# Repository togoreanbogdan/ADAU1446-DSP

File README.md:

# ADAU1446-DSP
Project for ADAU1446 Audio DSP. The PCB is compatible with all the family ADAU144x.

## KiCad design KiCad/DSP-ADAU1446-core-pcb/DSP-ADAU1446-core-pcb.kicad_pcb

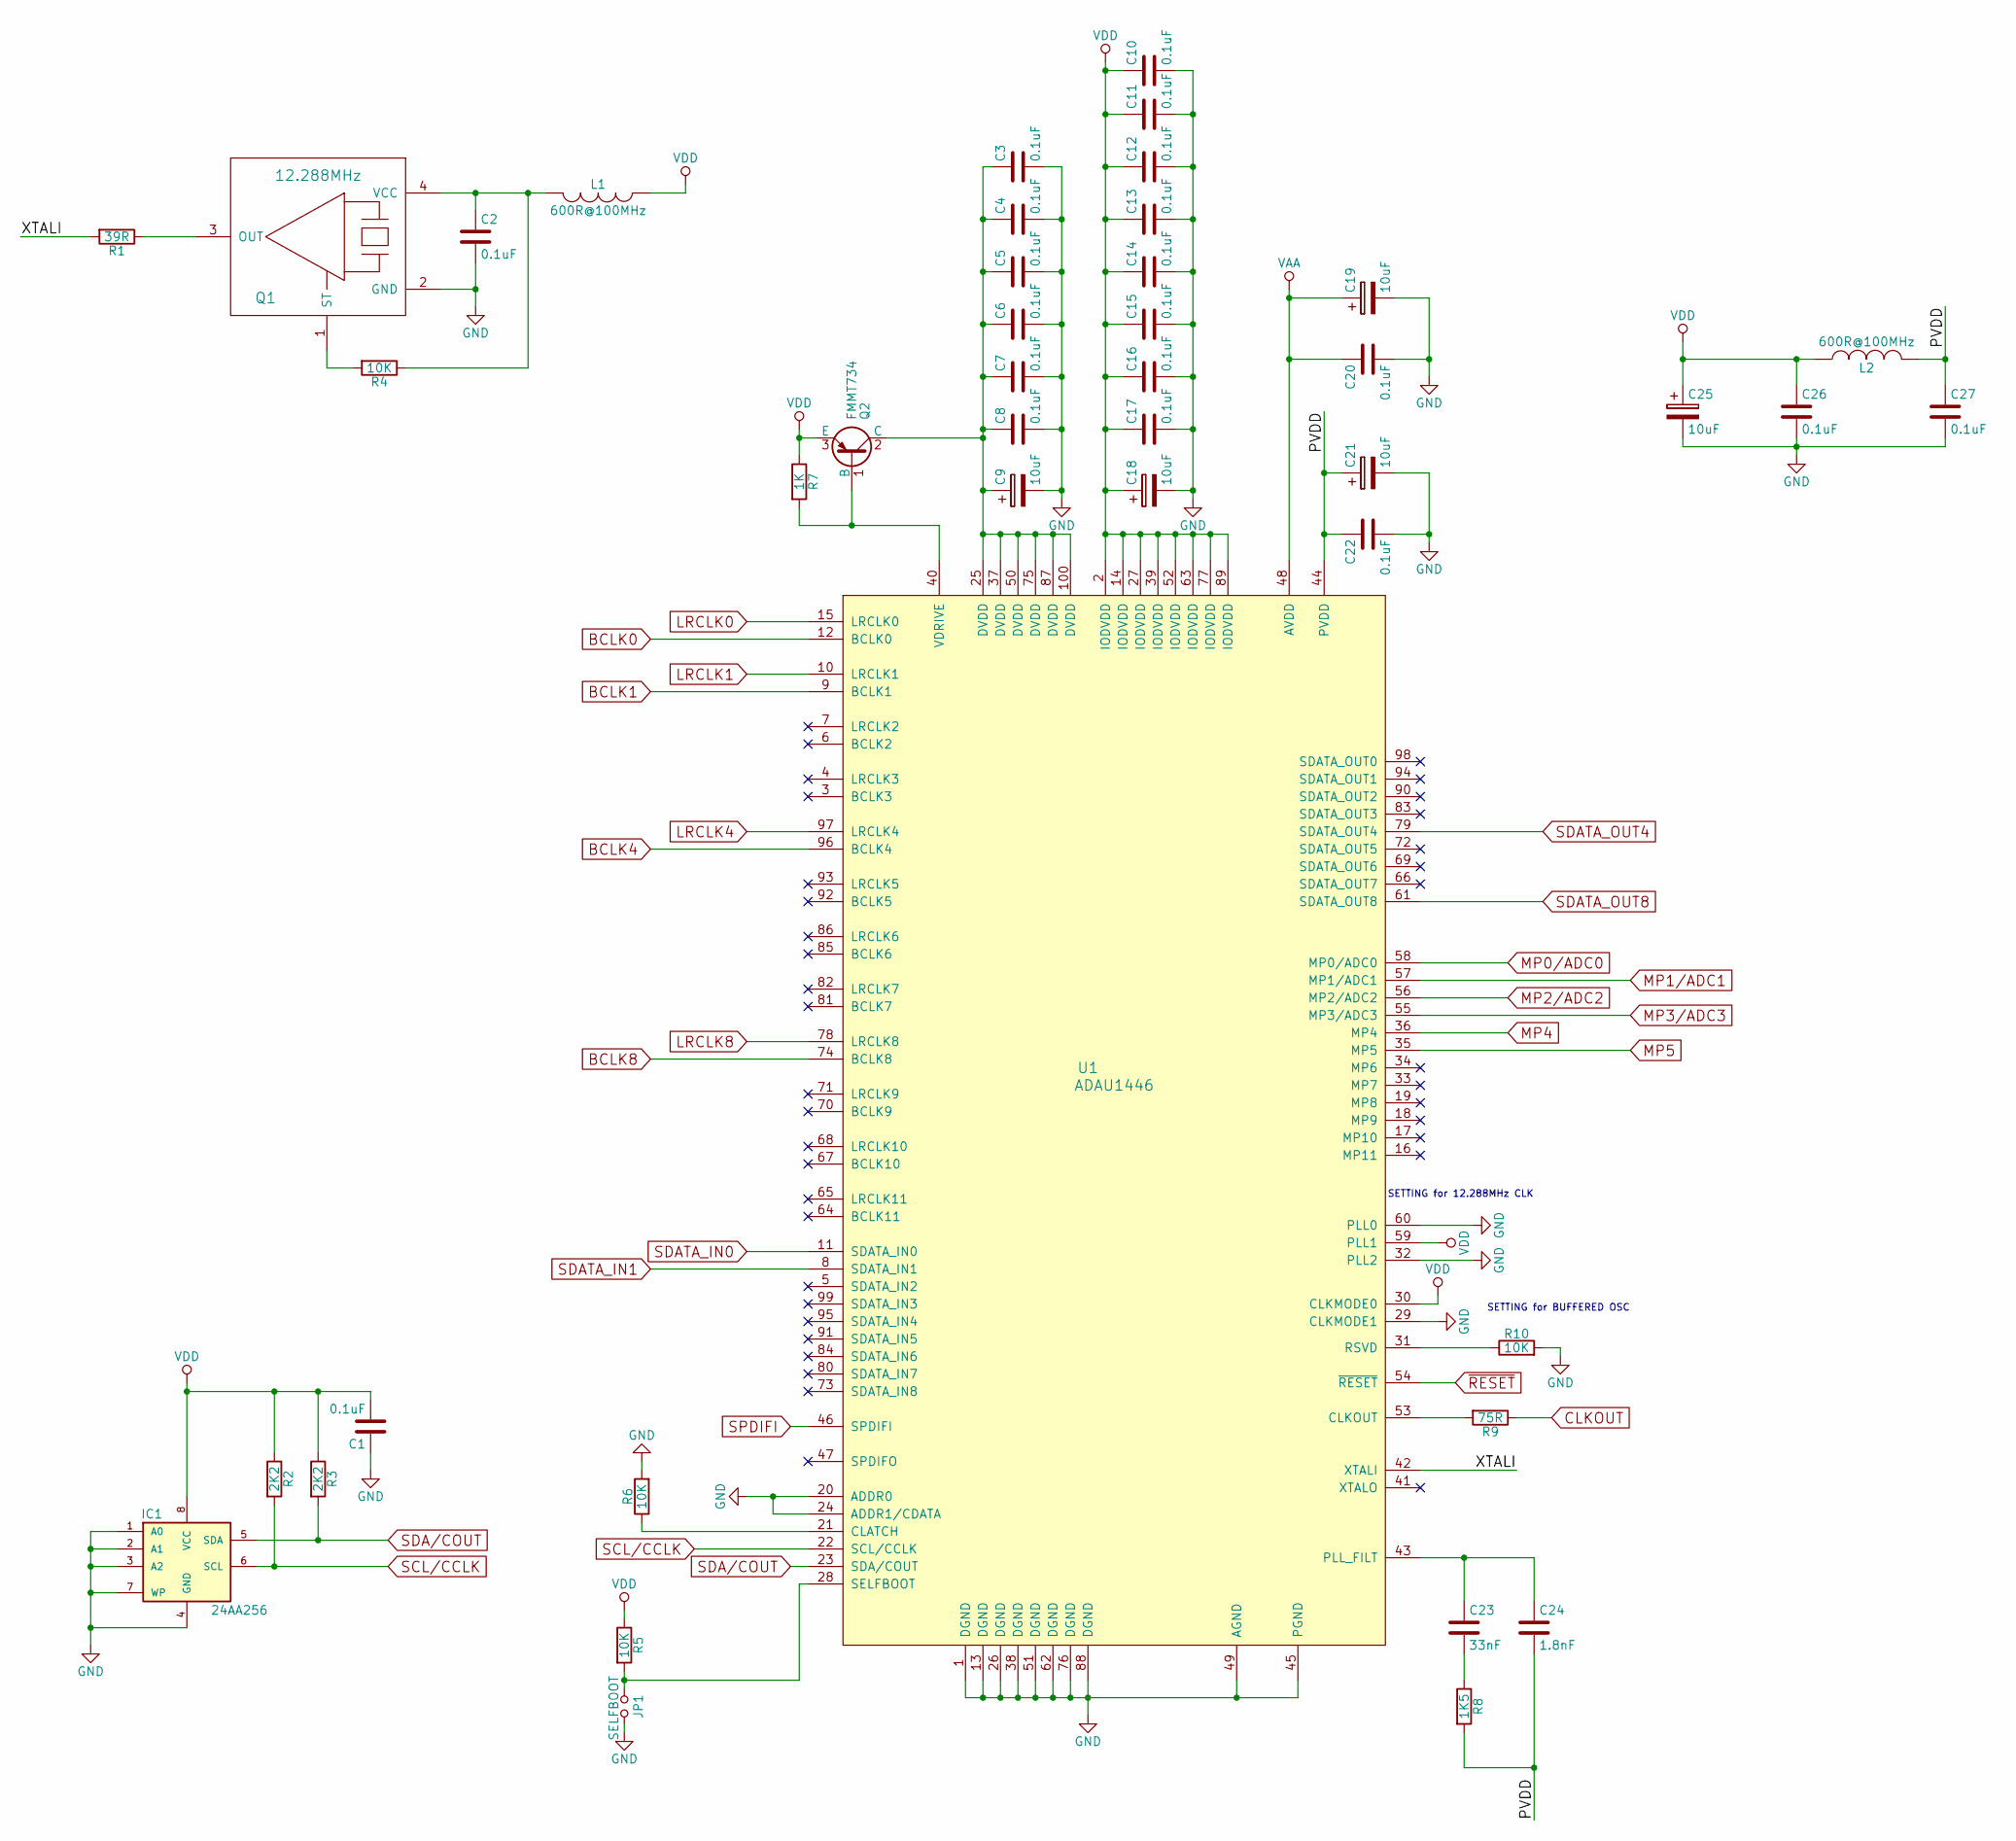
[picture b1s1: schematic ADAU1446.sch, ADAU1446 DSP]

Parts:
C1, C2, C3, C4, C5, C6, C7, C8, C10, C11, C12, C13, C14, C15, C16, C17, C20, C22, C26, C27: 0.1uF; c_0603
C9, C18: 10uF; c_elec_4x5.3; Mfr. Part No. EEE-FC1C100R
C19, C21, C25: 10uF; c_elec_4x5.3
C23: 33nF; c_0603
C24: 1.8nF; c_0603
IC1: 24AA256; so-8
JP1: SELFBOOT; pin_socket_2
L1, L2: 600R@100MHz; inductor_smd_0603
Q1: 12.288MHz; crystal_epson; Mfr. Part No. SG-210STF 12.2880ML3
Q2: FMMT734; sot23
R1: 39R; r_0603
R2, R3: 2K2; r_0603
R4, R5, R6, R10: 10K; r_0603
R7: 1K; r_0603
R8: 1K5; r_0603
R9: 75R; r_0603
U1: ADAU1446; TQFP-100

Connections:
/ADAU1446/PVDD: C21.1, C22.1, C24.2, C27.1, L2.2, R8.2, U1.44 (PVDD)
/ADAU1446/XTALI: R1.2, U1.42 (XTALI)
BCLK0: U1.12 (BCLK0); also elsewhere on the board
BCLK1: U1.9 (BCLK1); also elsewhere on the board
BCLK4: U1.96 (BCLK4); also elsewhere on the board
BCLK8: U1.74 (BCLK8); also elsewhere on the board
CLKOUT: R9.1; also elsewhere on the board
GND: C1.1, C2.2, C3.2, C4.2, C5.2, C6.2, C7.2, C8.2, C9.2, C10.2, C11.2, C12.2, C13.2, C14.2, C15.2, C16.2, C17.2, C18.2, C19.2, C20.2, C21.2, C22.2, C25.2, C26.2, C27.2, IC1.1 (A0), IC1.2 (A1), IC1.3 (A2), IC1.4 (GND), IC1.7 (WP), JP1.2, Q1.2 (GND), R6.2, R10.2, U1.1 (DGND), U1.13 (DGND), U1.20 (ADDR0), U1.24 (ADDR1/CDATA), U1.26 (DGND), U1.29 (CLKMODE1), U1.32 (PLL2), U1.38 (DGND), U1.45 (PGND), U1.49 (AGND), U1.51 (DGND), U1.60 (PLL0), U1.62 (DGND), U1.76 (DGND), U1.88 (DGND); also elsewhere on the board
LRCLK0: U1.15 (LRCLK0); also elsewhere on the board
LRCLK1: U1.10 (LRCLK1); also elsewhere on the board
LRCLK4: U1.97 (LRCLK4); also elsewhere on the board
LRCLK8: U1.78 (LRCLK8); also elsewhere on the board
MP0/ADC0: U1.58 (MP0/ADC0); also elsewhere on the board
MP1/ADC1: U1.57 (MP1/ADC1); also elsewhere on the board
MP2/ADC2: U1.56 (MP2/ADC2); also elsewhere on the board
MP3/ADC3: U1.55 (MP3/ADC3); also elsewhere on the board
MP4: U1.36 (MP4); also elsewhere on the board
MP5: U1.35 (MP5); also elsewhere on the board
unnamed: C2.1, L1.2, Q1.4 (VCC), R4.1
unnamed: C3.1, C4.1, C5.1, C6.1, C7.1, C8.1, C9.1, Q2.2 (C), U1.25 (DVDD), U1.37 (DVDD), U1.50 (DVDD), U1.75 (DVDD), U1.87 (DVDD), U1.100 (DVDD)
unnamed: C23.1, C24.1, U1.43 (PLL_FILT)
unnamed: C23.2, R8.1
unnamed: JP1.1, R5.2, U1.28 (SELFBOOT)
unnamed: Q1.1 (ST), R4.2
unnamed: Q1.3 (OUT), R1.1
unnamed: Q2.1 (B), R7.2, U1.40 (VDRIVE)
unnamed: R6.1, U1.21 (CLATCH)
unnamed: R9.2, U1.53 (CLKOUT)
unnamed: R10.1, U1.31 (RSVD)
SCL/CCLK: IC1.6 (SCL), R2.2, U1.22 (SCL/CCLK); also elsewhere on the board
SDA/COUT: IC1.5 (SDA), R3.2, U1.23 (SDA/COUT); also elsewhere on the board
SDATA_IN0: U1.11 (SDATA_IN0); also elsewhere on the board
SDATA_IN1: U1.8 (SDATA_IN1); also elsewhere on the board
SDATA_OUT4: U1.79 (SDATA_OUT4); also elsewhere on the board
SDATA_OUT8: U1.61 (SDATA_OUT8); also elsewhere on the board
SPDIFI: U1.46 (SPDIFI); also elsewhere on the board
VAA: C19.1, C20.1, U1.48 (AVDD); also elsewhere on the board
VDD: C1.2, C10.1, C11.1, C12.1, C13.1, C14.1, C15.1, C16.1, C17.1, C18.1, C25.1, C26.1, IC1.8 (VCC), L1.1, L2.1, Q2.3 (E), R2.1, R3.1, R5.1, R7.1, U1.2 (IODVDD), U1.14 (IODVDD), U1.27 (IODVDD), U1.30 (CLKMODE0), U1.39 (IODVDD), U1.52 (IODVDD), U1.59 (PLL1), U1.63 (IODVDD), U1.77 (IODVDD), U1.89 (IODVDD); also elsewhere on the board
~RESET: U1.54 (~RESET); also elsewhere on the board

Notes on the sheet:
SETTING for 12.288MHz CLK
SETTING for BUFFERED OSC

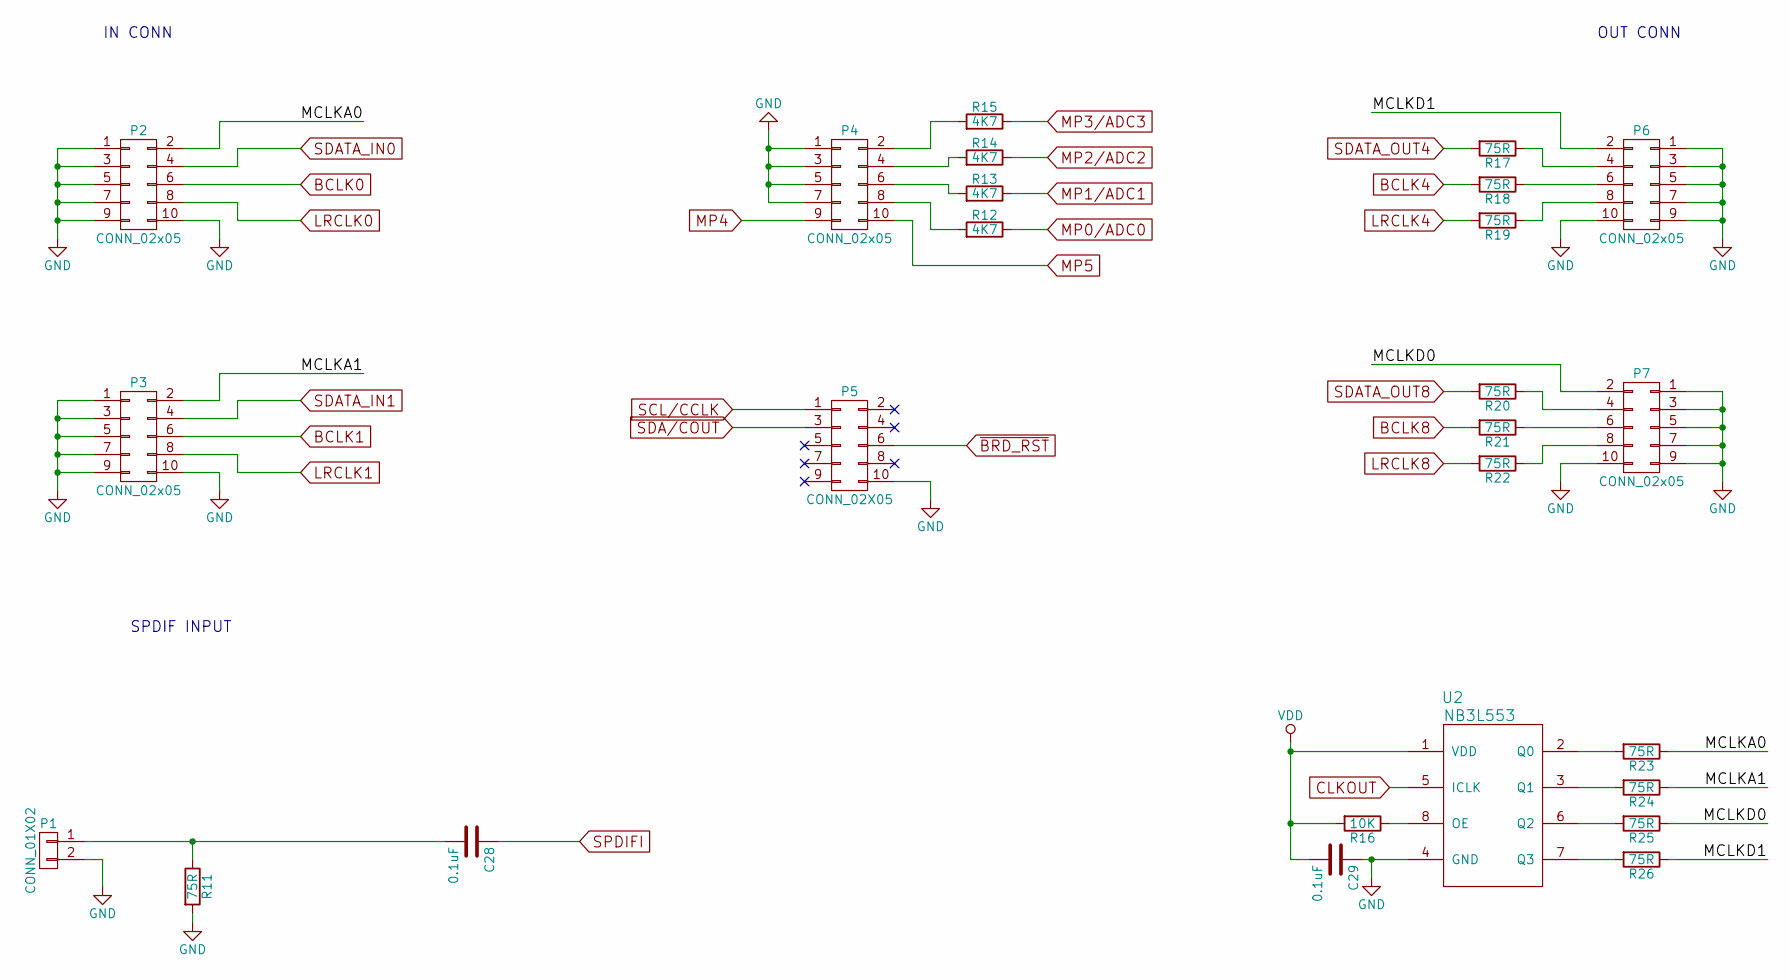
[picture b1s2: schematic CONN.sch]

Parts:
C28, C29: 0.1uF; c_0603
P1: CONN_01X02; Socket_Strip_Straight_1x02_Pitch2.54mm
P2, P3, P4, P6, P7: CONN_02x05; pin_strip_2mm_5x2; Mfr. Part No. DS1018-02-10B2
P5: CONN_02X05; pin_strip_2mm_5x2; Mfr. Part No. DS1018-02-10B2
R11, R17, R18, R19, R20, R21, R22, R23, R24, R25, R26: 75R; r_0603
R12, R13, R14, R15: 4K7; r_0603
R16: 10K; r_0603
U2: NB3L553; so-8; Mfr. Part No. NB3L553DG

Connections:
/CONN/MCLKA0: P2.2, R23.1
/CONN/MCLKA1: P3.2, R24.1
/CONN/MCLKD0: P7.2, R25.1
/CONN/MCLKD1: P6.2, R26.1
BCLK0: P2.6; also elsewhere on the board
BCLK1: P3.6; also elsewhere on the board
BCLK4: R18.2; also elsewhere on the board
BCLK8: R21.2; also elsewhere on the board
CLKOUT: U2.5 (ICLK); also elsewhere on the board
GND: C29.1, P1.2, P2.1, P2.3, P2.5, P2.7, P2.9, P2.10, P3.1, P3.3, P3.5, P3.7, P3.9, P3.10, P4.1, P4.3, P4.5, P4.7, P5.10, P6.1, P6.3, P6.5, P6.7, P6.9, P6.10, P7.1, P7.3, P7.5, P7.7, P7.9, P7.10, R11.2, U2.4 (GND); also elsewhere on the board
LRCLK0: P2.8; also elsewhere on the board
LRCLK1: P3.8; also elsewhere on the board
LRCLK4: R19.2; also elsewhere on the board
LRCLK8: R22.2; also elsewhere on the board
MP0/ADC0: R12.1; also elsewhere on the board
MP1/ADC1: R13.1; also elsewhere on the board
MP2/ADC2: R14.1; also elsewhere on the board
MP3/ADC3: R15.1; also elsewhere on the board
MP4: P4.9; also elsewhere on the board
MP5: P4.10; also elsewhere on the board
unnamed: C28.2, P1.1, R11.1
unnamed: P4.2, R15.2
unnamed: P4.4, R14.2
unnamed: P4.6, R13.2
unnamed: P4.8, R12.2
unnamed: P6.4, R17.1
unnamed: P6.6, R18.1
unnamed: P6.8, R19.1
unnamed: P7.4, R20.1
unnamed: P7.6, R21.1
unnamed: P7.8, R22.1
unnamed: R16.1, U2.8 (OE)
unnamed: R23.2, U2.2 (Q0)
unnamed: R24.2, U2.3 (Q1)
unnamed: R25.2, U2.6 (Q2)
unnamed: R26.2, U2.7 (Q3)
SCL/CCLK: P5.1; also elsewhere on the board
SDA/COUT: P5.3; also elsewhere on the board
SDATA_IN0: P2.4; also elsewhere on the board
SDATA_IN1: P3.4; also elsewhere on the board
SDATA_OUT4: R17.2; also elsewhere on the board
SDATA_OUT8: R20.2; also elsewhere on the board
SPDIFI: C28.1; also elsewhere on the board
VDD: C29.2, R16.2, U2.1 (VDD); also elsewhere on the board
~BRD_RST: P5.6; also elsewhere on the board

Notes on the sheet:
OUT CONN
IN CONN
SPDIF INPUT

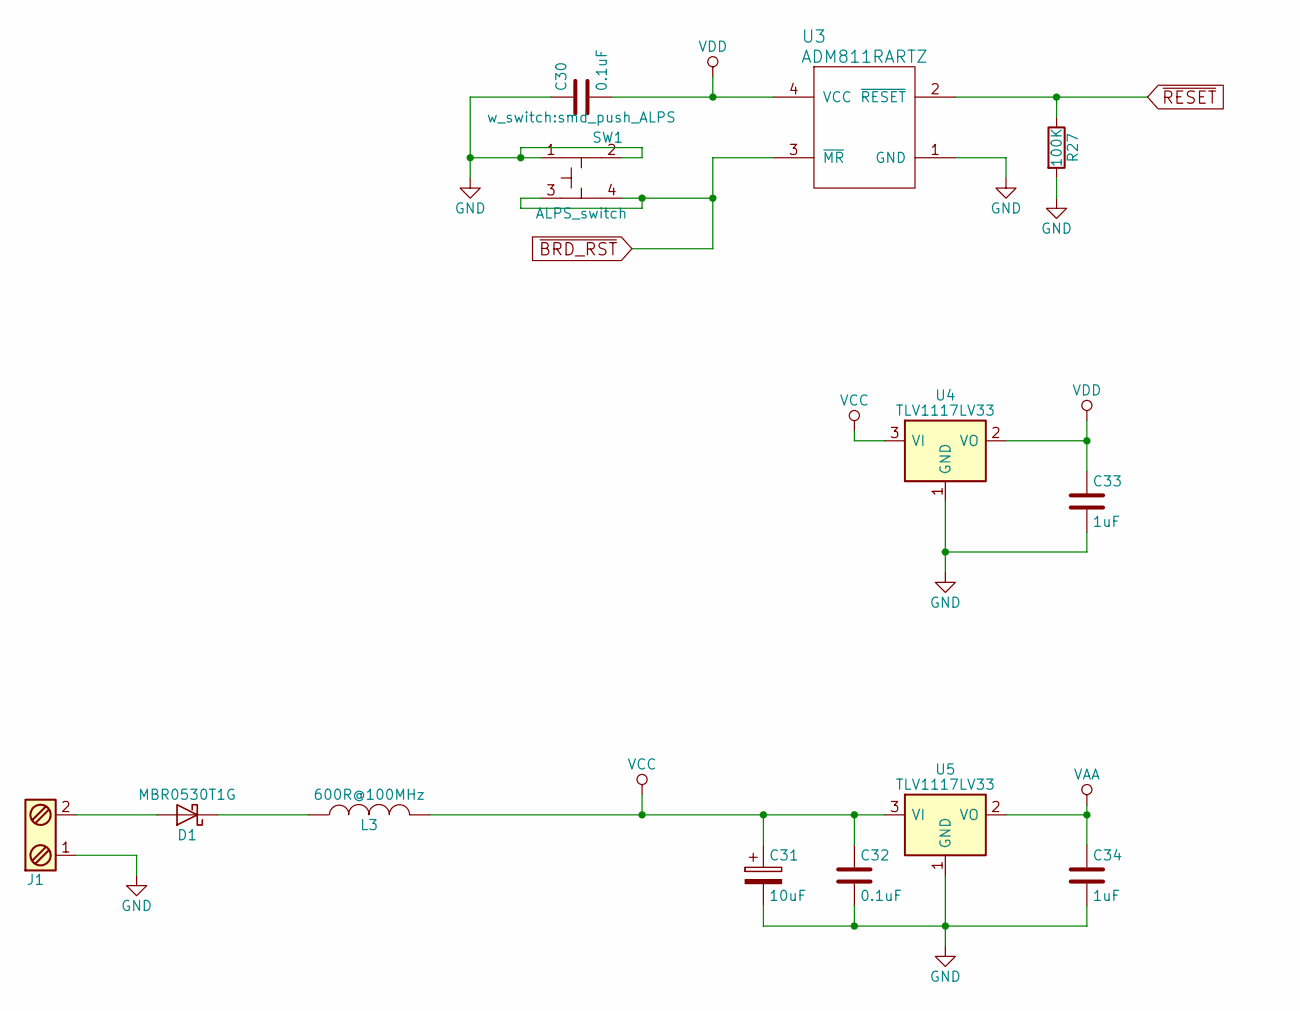
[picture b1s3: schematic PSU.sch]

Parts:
C30, C32: 0.1uF; c_0603
C31: 10uF; c_elec_4x5.3; Mfr. Part No. EEE-FC1C100R
C33, C34: 1uF; c_0805
D1: MBR0530T1G; sod123
J1: POW_CONN; mkds_1,5-2
L3: 600R@100MHz; inductor_smd_0603
R27: 100K; r_0603
SW1: ALPS_switch; smd_push_ALPS
U3: ADM811RARTZ; sot143B
U4, U5: TLV1117LV33; SOT-223-3Lead_TabPin2

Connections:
GND: C30.1, C31.2, C32.2, C33.2, C34.2, J1.1, R27.2, SW1.1, SW1.2, U3.1 (GND), U4.1 (GND), U5.1 (GND); also elsewhere on the board
unnamed: D1.1 (K), L3.1
unnamed: D1.2 (A), J1.2
VAA: C34.1, U5.2 (VO); also elsewhere on the board
VCC: C31.1, C32.1, L3.2, U4.3 (VI), U5.3 (VI)
VDD: C30.2, C33.1, U3.4 (VCC), U4.2 (VO); also elsewhere on the board
~BRD_RST: SW1.3, SW1.4, U3.3 (~MR); also elsewhere on the board
~RESET: R27.1, U3.2 (~RESET); also elsewhere on the board

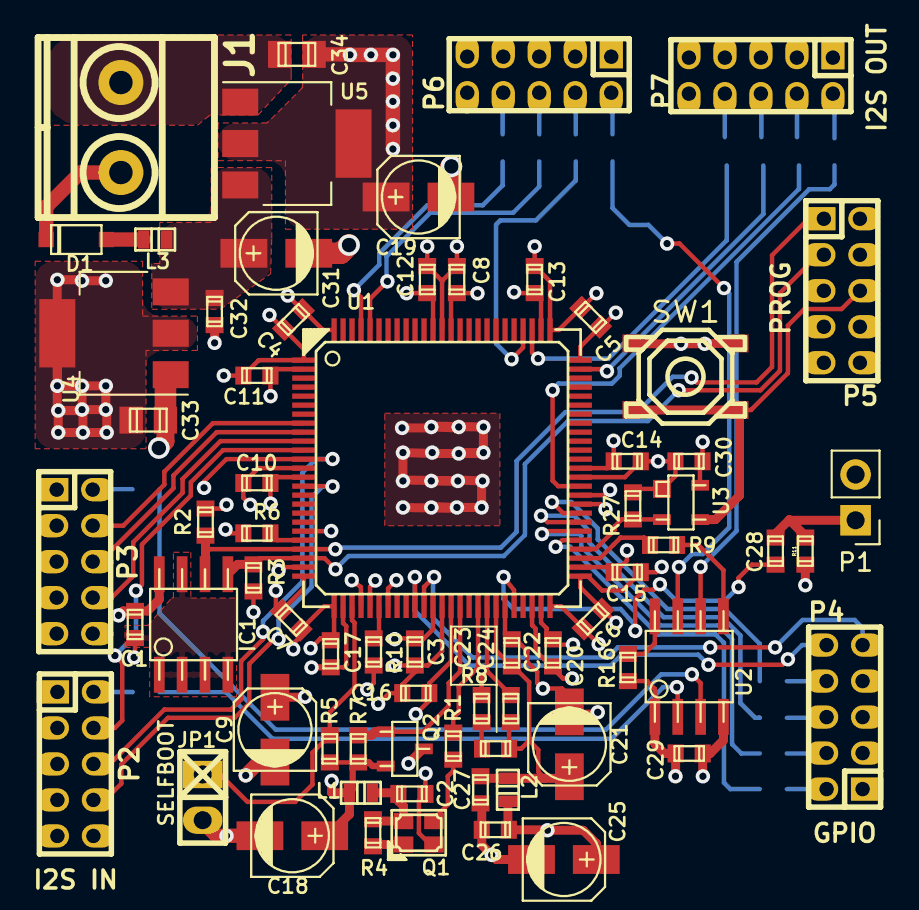
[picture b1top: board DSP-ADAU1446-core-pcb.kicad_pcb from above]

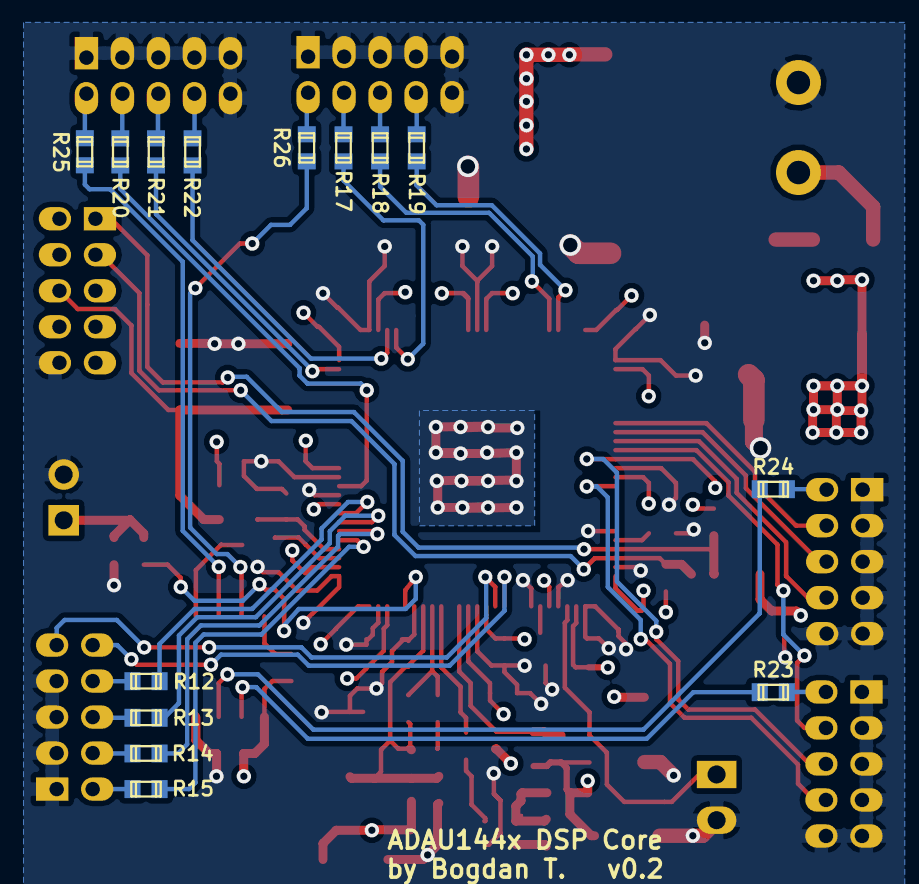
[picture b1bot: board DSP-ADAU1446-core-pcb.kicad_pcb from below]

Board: 4 copper layers, 83 parts (14 on the bottom side), 63 nets.

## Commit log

2017-01-30 Initial commit. Work started on core DSP schematic
2017-01-30 - added switches library - updated ADAU1446 DSP core schematic
2017-02-12 - finished schematics v0.1 - PCB work began - BOM generated
2017-02-19 - modifyed regulator transistor
2017-02-19 - pcb development update
2017-02-20 Update .gitignore
    Allow track of BOM files
2017-02-22 -pcb update - changed footprint of IC1 and U2 to SO8
2017-03-05 finished schematic and PCB for v0.1
2017-03-05 updated .gitnore to allow BOM .xml
2017-03-05 added production GERBER files
2017-03-05 updated .csv BOM
2017-03-05 added Mouser Part Numbers BOM
2017-08-31 Updated schematic and PCB to use SDATA_OUT4 and SDATA_OUT8 with LRCLK4,LRCLK8 and BCLK8,BCLK8
2017-08-31 Added gerber files for V0.2
